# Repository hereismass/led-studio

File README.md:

# LED Studio

The phased editor implementation is tracked in the [editor UI roadmap](docs/editor-roadmap.md).

LED Studio is a Mac-first desktop editor for lighting projects targeting configurable LED hardware. The first hardware profile represents a KMS Thunderbird-style four-string bass with 10 independently addressable RGB LEDs, but the project format is intentionally not instrument-specific.

This repository is a pnpm workspace so it can also contain controller firmware and supporting tools in the future.

## Repository layout

- `apps/desktop` — Tauri v2, React, and TypeScript desktop application
- `firmware/controller` — Zephyr controller application and portable C runtime
- `packages/project-format` — UI-independent project validation and TypeScript types
- `packages/editor-core` — UI-independent project creation, editor commands, and bounded grouped history
- `packages/hardware-profiles` — UI-independent hardware geometry, addressing, groups, and compatibility validation
- `packages/playback` — UI-independent scene evaluation and deterministic song/cue transport
- `examples` — example LED Studio project files

## Prerequisites

- Node.js `^20.19.0` or `>=22.12.0`
- pnpm 11
- Rust 1.88 or newer and Cargo (the repository includes a rustup toolchain file)
- On macOS, Xcode Command Line Tools

The root pnpm scripts place rustup's standard Cargo directory first on macOS, avoiding conflicts when another version manager such as mise also provides a `cargo` shim.

## Install and run

```sh
pnpm install
pnpm dev
```

The second command starts the Vite development server and opens it in a Tauri window.

On startup, choose to create an untitled project, open and validate a local project, or load a bundled example as an unsaved template. Save atomically replaces the current file, while Save As chooses a new `.ledstudio` destination. New and example-derived projects use Save As for their first save. The app also accepts `.json` files when opening. Closing the window or quitting prompts before discarding unsaved work.

Inside a project, the name, preview BPM, time signature, linked palette colours, reusable LED groups, scenes, and songs are editable. New projects start with a four-beat `Scene 1` in which every profile LED is white at full brightness, plus `Song 1` with a manual cue for that shared scene. Palette tokens, groups, scenes, songs, cues, layers, and keyframes have hidden, stable UUIDs. A scene combines sparse static LED assignments with ordered Pulse, Chase, Wave, Sparkle, and keyframe layers; every layer can target LEDs directly or remain linked to built-in or project groups. Static LEDs at zero brightness retain their palette link, while the explicit off action removes the assignment. Project edits support Undo and Redo from the toolbar or with <kbd>⌘Z</kbd> and <kbd>⌘⇧Z</kbd> on macOS. History retains the latest 200 undo steps; live controls and timeline drags are grouped into one undoable interaction.

The KMS profile renders an interactive, physically proportioned four-string fretboard with 10 LEDs and built-in E-side and G-side selection groups. The editor numbers them from fret 3 toward fret 21. Independently, the electrical chain starts at fret 21 on the G side, crosses to the E side at fret 12, and ends at fret 3.

The active scene can be previewed with Play/Pause, Stop, and the Scene Timeline scrubber. Preview playback loops at the project BPM, updates immediately while scene LEDs, groups, layers, keyframes, or timing are edited, and remains transient rather than changing the project file. Layer rows can be dragged vertically to change compositing order. Chase and Wave travel through profile-defined visual positions from fret 3 toward fret 21; the two LEDs at fret 12 share one position and therefore move together when both are targeted. Their loop-length controls describe a complete repeating cycle, while deterministic Sparkle patterns remain independent per physical LED and can hold or fade between steps. The Add Layer menu also offers Slow Breath, Comet, Rolling Wave, and Soft Twinkle quick starts; these create ordinary editable layers rather than persisted preset references. Keyframe layers disclose independent brightness and linked palette-colour tracks; keys are authored at the snapped playhead, and each outgoing segment supports Linear, Ease In, Ease Out, or Ease In/Out shaping. Colour tracks support smooth RGB or step interpolation, with Step deliberately ignoring stored easing. A keyframe layer's start/end window masks stored keys without moving or deleting them. The timeline supports quarter-, half-, whole-beat, and bar snapping plus persistent manual zoom or Fit Scene. Offscreen labels and keyframe controls are omitted from the DOM while scrolling large loops.

Songs are ordered project assets that arrange shared scenes as cues without copying scene content. Each song owns its preview tempo, time signature, and launch quantization (`Immediate`, `Next beat`, or `Next bar`). A cue either waits for manual advancement or advances after a configured number of complete scene loops; the final cue keeps looping. Selecting a cue previews its referenced scene, while deleting a scene that is still used by any cue is rejected. Song order is the future controller browse order; setlists and external mappings remain separate deferred concepts.

Keyframes in one layer can be selected across both tracks with <kbd>⌘</kbd>/<kbd>Ctrl</kbd>-click, extended in one track with <kbd>Shift</kbd>-click, or selected together with <kbd>⌘A</kbd>/<kbd>Ctrl+A</kbd> after focusing the layer. Dragging or using the arrow keys moves the selection as one undoable edit. Layers and keyframe selections support contextual Copy, Cut, Paste, Duplicate, and Delete actions. The in-app clipboard lasts for the current app session, including project switches, but is neither persisted nor shared with the system clipboard. Cross-project paste preserves exact palette IDs, falls back to an exact colour value, and validates hardware targets before making an atomic change.

Press <kbd>Space</kbd> to toggle playback when focus is not inside an interactive editor control. Timeline shortcuts include <kbd>⌘C</kbd>/<kbd>⌘X</kbd>/<kbd>⌘V</kbd>, <kbd>⌘D</kbd>, Delete, <kbd>⌘+</kbd>/<kbd>⌘−</kbd>, and <kbd>⌘0</kbd> for Fit Scene; use Ctrl instead of Command on non-macOS platforms. Static scenes stay off the animation-frame render path; animated scenes use the UI-independent evaluator.

## Tests and checks

```sh
pnpm test
pnpm test:rust
pnpm typecheck
pnpm build:web
pnpm check:rust
pnpm format:check
pnpm lint
```

Run all non-bundling checks together with:

```sh
pnpm check
```

The portable controller runtime can also be tested independently with:

```sh
pnpm test:firmware
```

For repeatable microbenchmarks of the large editor-command and playback paths:

```sh
pnpm benchmark
```

To produce a native application bundle:

```sh
pnpm build
```

## Project format

Version 2 contains a schema version, required project name, opaque hardware-profile identifier, project-wide standalone preview timing, linked palette tokens, project-wide LED groups, shared scenes, and ordered songs. Each song has timing, launch quantization, and ordered cues that reference scenes. Scenes have unique UUIDs and names, a loop length in quarter-beat steps, sparse static LED assignments with brightness from zero to 100, and ordered typed scene layers. Effect layers contain Pulse, Chase, Wave, or deterministic Sparkle parameters. Keyframe layers contain independently optional brightness and linked palette-colour tracks with ordered quarter-beat keys. Every key stores the easing for its outgoing segment; omitted easing defaults to Linear. Version 1 files remain intentionally unsupported; schema v2 may continue changing without migrations during active development.

Hardware profiles describe canonical editor order, grouped effect positions, electrical addresses, and physical layout separately; the project format does not embed instrument-specific geometry.

Project files are JSON documents validated at runtime with Zod and use the `.ledstudio` extension. See [`examples/kms-4-string-10-led-v1.ledstudio`](examples/kms-4-string-10-led-v1.ledstudio).

To keep editing and playback responsive when opening untrusted local files, v2 currently caps projects at 32 MiB, 4,096 loop beats, 256 palette tokens, groups, scenes, and songs, 512 layers per scene and cues per song, 4,096 keys per track and loops per automatic cue, and 50,000 total project entities. These are generous development safeguards rather than a frozen compatibility policy.

## Deliberately out of scope

There is currently no palette or scene reordering, setlist model, autosave, recovery backup, native File menu, system clipboard integration, custom effect presets, freeform keyframe curve editor, blend modes, MIDI or Ableton integration, external clock, Bluetooth, USB communication, OLED or footswitch support, device-package export, external backend, cloud service, account system, database, or external API. Controller firmware is at its initial hard-coded bring-up stage and cannot yet load editor projects.

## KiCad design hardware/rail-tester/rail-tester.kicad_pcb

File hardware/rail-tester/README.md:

# 5-pixel rigid rail tester

This is the first functional prototype for the bass fingerboard LEDs. It is deliberately **not** the final flex PCB: it tests the exact LED package, power voltage, data chain, two-rail wiring, and diffusion before committing to the final fret spacing and flexible construction.

Order four identical boards: two for the actual two-rail test and two spares. Each board is 49.5 x 14 mm, 0.8 mm thick, 2-layer rigid FR-4, with five addressable RGB LEDs at a deliberately simple 7 mm pitch.

## Electrical layout

`VLED/GND/DIN IN` enters at J1. `DIN` passes through R1 (330 ohm) into D1, then chains through D5. TP1 exposes the final `DOUT` for diagnosis only. C1 is the input capacitor and C2-C6 provide local bypassing at each LED.

Use one controller data output for each board. The controller and both boards must share ground. Do not use a controller board's low-current 3.3 V pin to power the LEDs; provide a regulated LED supply suitable for the test current. At full white, budget up to 180 mA per board and 360 mA for the two-board test; use a supply rated for at least 0.5 A total with current limiting.

## Assembly request

Upload `rail-tester.kicad_pcb` to AISLER and request top-side assembly. Use 0.8 mm, 2-layer rigid FR-4. The supplied `rail-tester-bom.csv` is the human-readable assembly reference; confirm the imported parts in AISLER's BOM Manager before checkout.

Before ordering, verify all of the following in AISLER's preview:

- D1-D5 are assigned to the exact Worldsemi `WS2812B-2020-V6` part, with the pin-1 orientation matching the board preview.
- R1 is a 330 ohm, 1%, 0603 resistor.
- C1 is a 1 uF, 10 V or higher, X5R/X7R, 0603 capacitor; C2-C6 are 100 nF, 10 V or higher, X5R/X7R, 0603 capacitors.
- D1-D5, R1, and C1-C6 are fitted. J1 and TP1 are excluded from assembly.

Supplying the V6 LEDs yourself is only a fallback if AISLER cannot procure that exact part. J1 and TP1 are intentional hand-solder pads: solder a three-conductor cable to J1 after assembly, then secure it to the board during testing with a small clamp or tape strain relief.

## Test plan

1. Connect each board to the controller with VLED/GND/DIN and a common ground. Add strain relief before moving the board.
2. Test the same animation at regulated 3.3 V and 5 V. Start with a conservative current limit and low software brightness, then increase gradually.
3. Compare brightness, colour consistency, and data reliability through a sample fingerboard diffuser.
4. Choose the final rail voltage only after this comparison.

The eventual bass build will use two long FPC rails at the final marker positions, not this 7 mm prototype spacing.

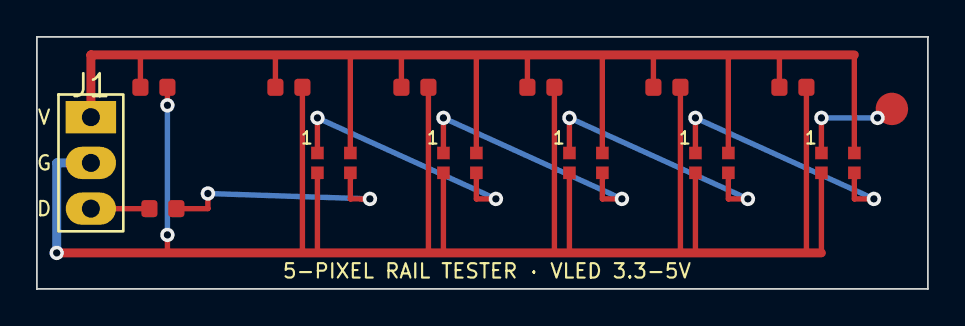
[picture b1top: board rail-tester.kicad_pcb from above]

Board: 2 copper layers, 49.5 x 14.0 mm, 14 parts (0 on the bottom side), 9 nets.

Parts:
C1: 1uF 10V; C_0603_1608Metric
C2, C3, C4, C5, C6: 100nF 10V; C_0603_1608Metric
D1, D2, D3, D4, D5: WS2812B-2020-V6; LED_WS2812B-2020_PLCC4_2.0x2.0mm
J1: VLED/GND/DIN; PinHeader_1x03_P2.54mm_Vertical
R1: 330R; R_0603_1608Metric
TP1: DOUT; TestPoint_Pad_D1.5mm

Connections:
+VLED: C1.1, C2.1, C3.1, C4.1, C5.1, C6.1, D1.4, D2.4, D3.4, D4.4, D5.4, J1.1
DIN_1: D1.3, R1.2
DIN_RAW: J1.3, R1.1
DOUT_1: D1.1, D2.3
DOUT_2: D2.1, D3.3
DOUT_3: D3.1, D4.3
DOUT_4: D4.1, D5.3
DOUT_5: D5.1, TP1.1
GND: C1.2, C2.2, C3.2, C4.2, C5.2, C6.2, D1.2, D2.2, D3.2, D4.2, D5.2, J1.2

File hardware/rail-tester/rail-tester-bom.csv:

Designator,Quantity,Value,Manufacturer part number,Notes
D1-D5,5,Addressable RGB LED,Worldsemi WS2812B-2020-V6,Ask AISLER to source and assemble this exact part; customer-supplied parts are a fallback only
R1,1,330 ohm 0603,Generic 1% 0603,Series data resistor
C1,1,1 uF 10 V X5R 0603,Generic 0603,Input bulk/bypass capacitor
C2-C6,5,100 nF 10 V X5R 0603,Generic 0603,One local bypass capacitor per LED
J1,1,3-pin solder pads,PCB feature,Exclude from assembly; hand-solder VLED/GND/DIN cable after assembly
TP1,1,DOUT solder test pad,PCB feature,Exclude from assembly; leave unconnected in normal use
